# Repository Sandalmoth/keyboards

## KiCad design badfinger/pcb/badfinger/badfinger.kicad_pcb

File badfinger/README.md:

# Badfinger

__Would not recommend building__, as I made a lot of design mistakes, but it is possible. 
It's a 52 key low-profile keyboard, with slightly bigger than choc spacing, powered by regular batteries. 
Ultimately, I wanted a wireless split powered by regular 1.2V AAA batteries, and it's what I got.

The most interesting takeaway here is that the R-78S3.3-0.1 is a really handy part for making battery powered things.

## Materials
__2x PCBs__

__2x XIAO nRF52840__  

__2x Keystone 2468 Battery holder__

__2x R-78S3.3-0.1 DC-DC converter__

Finally, some m3x10, m3x6, m3 square nuts, m2x8 self tapping screws, and wires for the assembly. 
There's also a 2.2uF cap and 1uH inductor, but, I think the inductor could be replaced by a wire and the cap skipped with no real harm done, though don't quote me on that.

The DC-DC converter won't fit in it's footprint, but needs to be connected with wires and placed just below the battery holder. Looking at the case std should make it fairly clear where it goes.

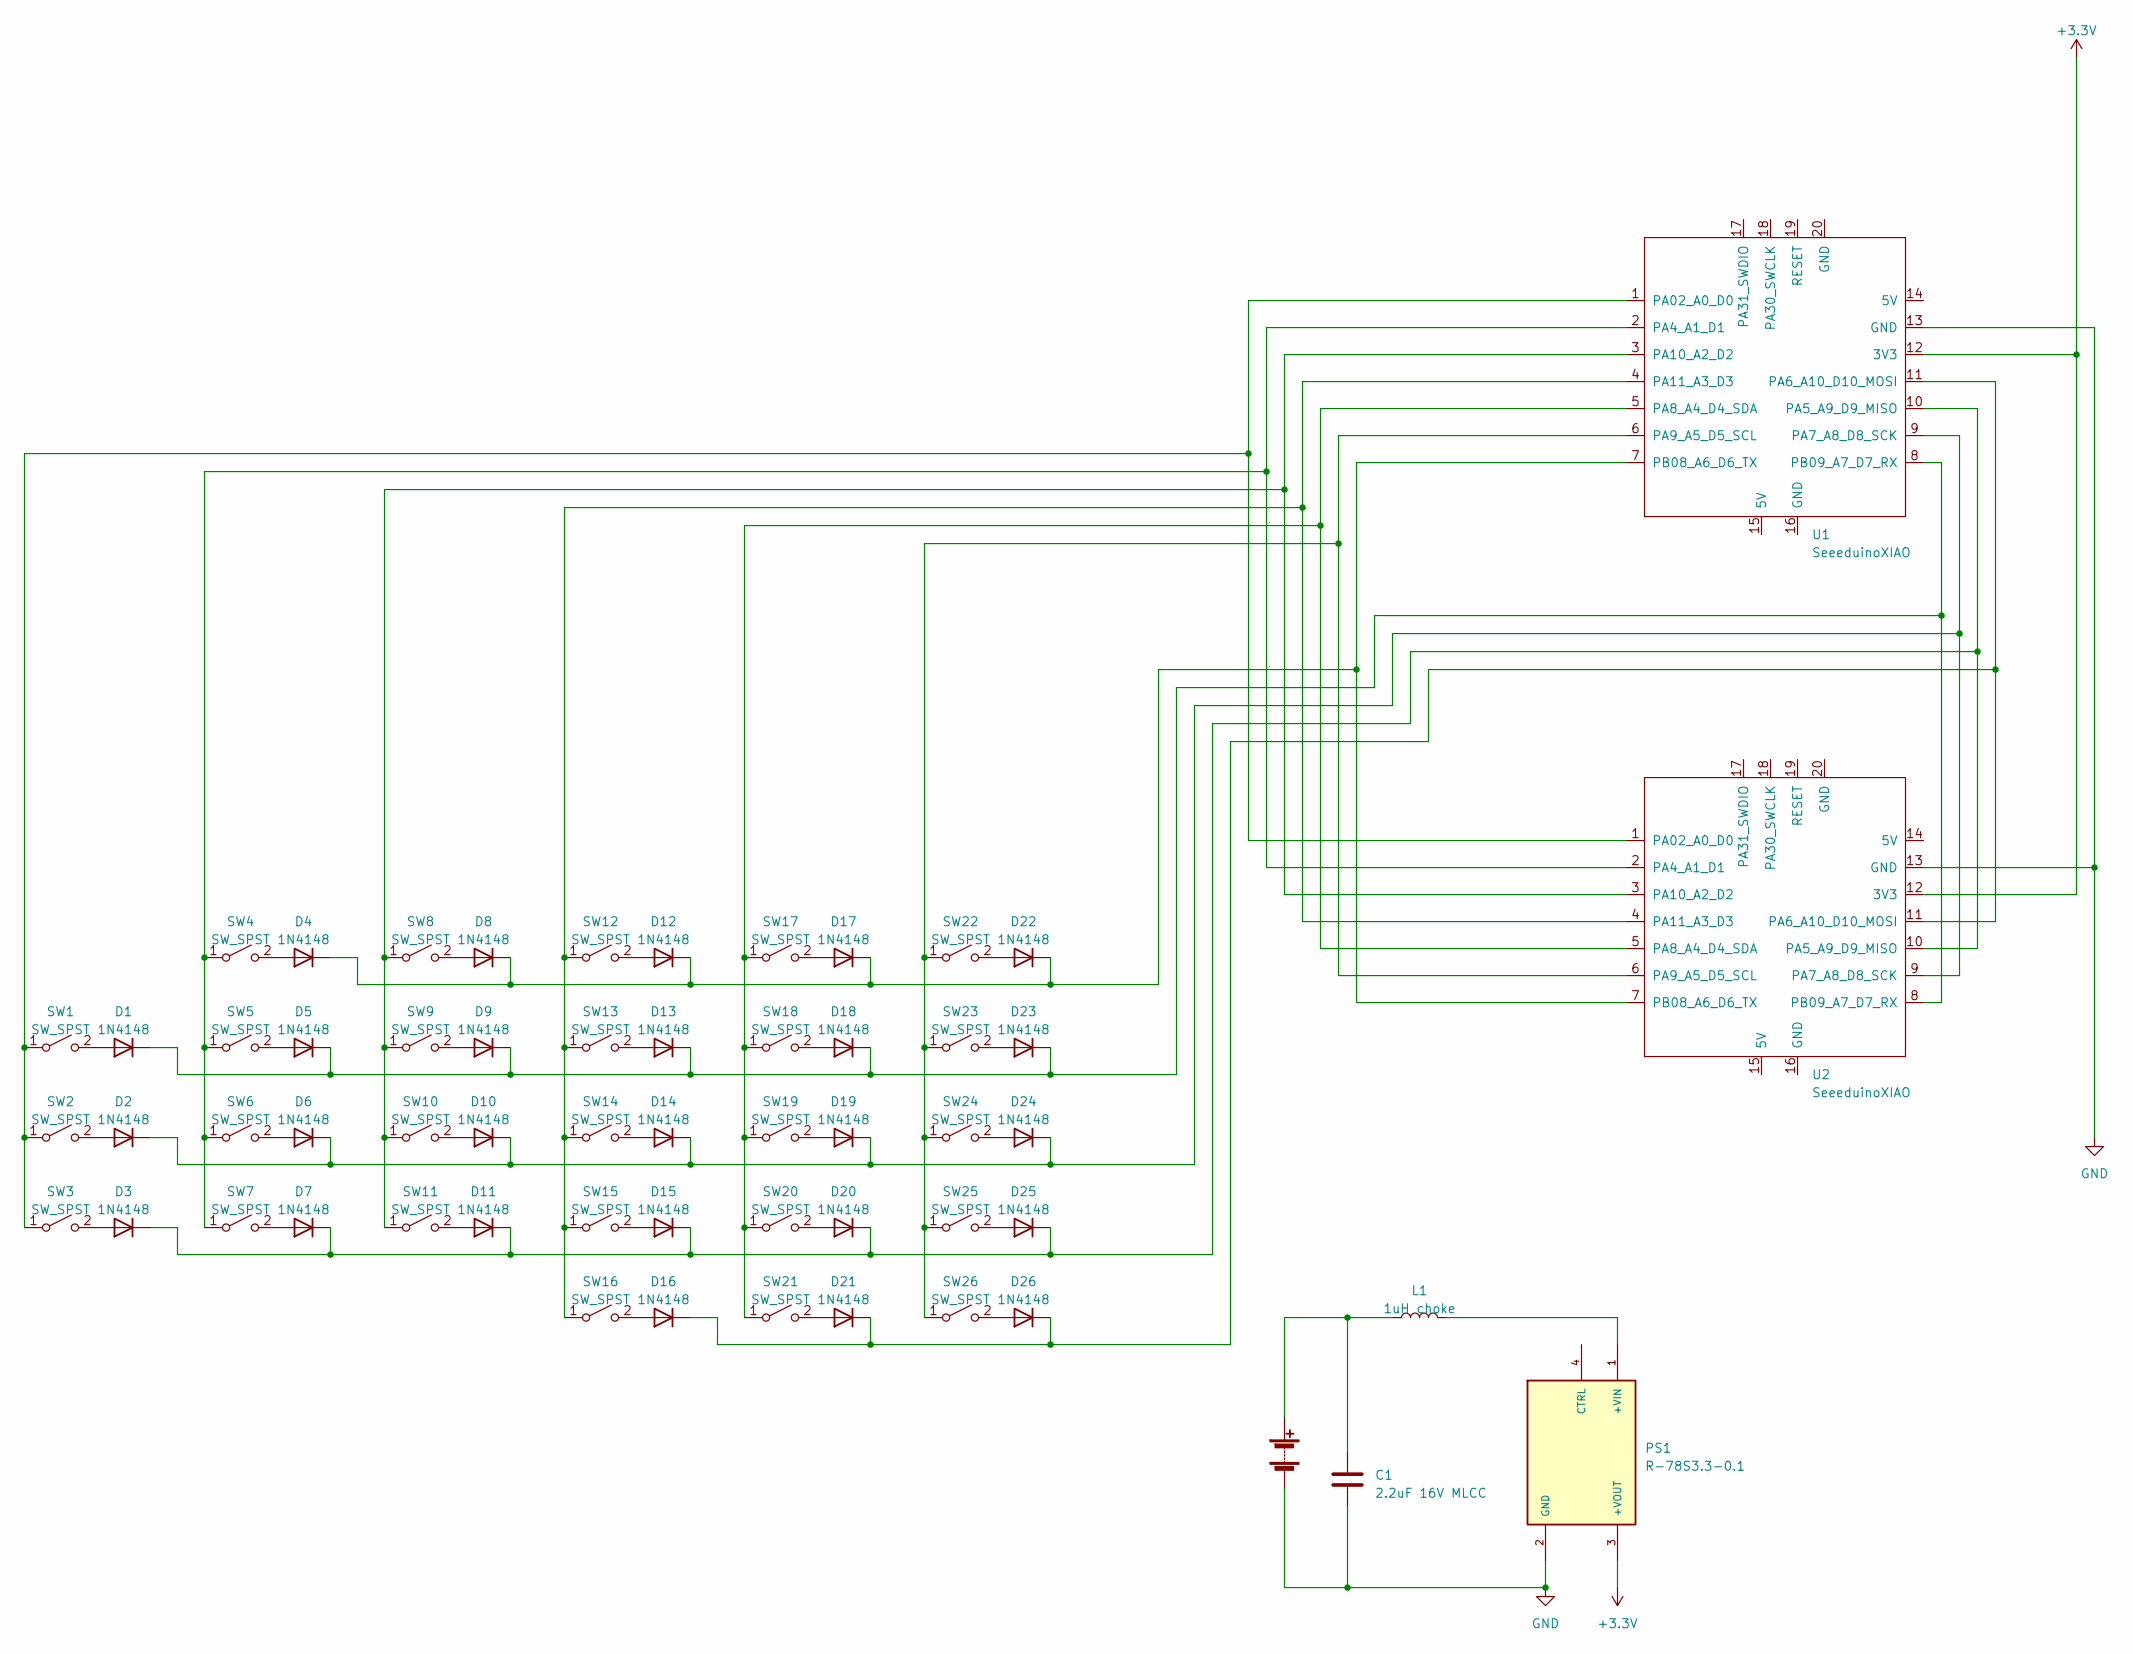
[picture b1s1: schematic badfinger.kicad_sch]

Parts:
BT1: Battery; PinHeader_1x02_P2.54mm_Vertical
C1: 2.2uF 16V MLCC; CP_Radial_D5.0mm_P2.50mm
D1, D2, D3, D4, D5, D6, D7, D8, D9, D10, D11, D12, D13, D14, D15, D16, D17, D18, D19, D20, D21, D22, D23, D24, D25, D26: 1N4148; D_DO-35_SOD27_P7.62mm_Horizontal
L1: 1uH choke; L_Axial_L9.5mm_D4.0mm_P15.24mm_Horizontal_Fastron_SMCC
PS1: R-78S3.3-0.1; CONV_R-78S3.3-0.1; PARTREV 5
SW1, SW2, SW3, SW4, SW5, SW6, SW7, SW8, SW9, SW10, SW11, SW12, SW13, SW14, SW15, SW16, SW17, SW18, SW19, SW20, SW21, SW22, SW23, SW24, SW25, SW26: SW_SPST; SW_PG1350_reversible
U1, U2: SeeeduinoXIAO; qtpy

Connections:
+3.3V: PS1.3 (+VOUT), U1.12 (3V3), U2.12 (3V3)
GND: BT1.2 (-), C1.2, PS1.2 (GND), U1.13 (GND), U2.13 (GND)
unnamed: BT1.1 (+), C1.1, L1.1
unnamed: D1.2 (A), SW1.2 (B)
unnamed: D1.1 (K), D5.1 (K), D9.1 (K), D13.1 (K), D18.1 (K), D23.1 (K), U1.8 (PB09_A7_D7_RX), U2.8 (PB09_A7_D7_RX)
unnamed: D2.2 (A), SW2.2 (B)
unnamed: D3.2 (A), SW3.2 (B)
unnamed: D4.2 (A), SW4.2 (B)
unnamed: D5.2 (A), SW5.2 (B)
unnamed: D6.2 (A), SW6.2 (B)
unnamed: D7.2 (A), SW7.2 (B)
unnamed: D8.2 (A), SW8.2 (B)
unnamed: D9.2 (A), SW9.2 (B)
unnamed: D10.2 (A), SW10.2 (B)
unnamed: D2.1 (K), D6.1 (K), D10.1 (K), D14.1 (K), D19.1 (K), D24.1 (K), U1.9 (PA7_A8_D8_SCK), U2.9 (PA7_A8_D8_SCK)
unnamed: D11.2 (A), SW11.2 (B)
unnamed: D3.1 (K), D7.1 (K), D11.1 (K), D15.1 (K), D20.1 (K), D25.1 (K), U1.10 (PA5_A9_D9_MISO), U2.10 (PA5_A9_D9_MISO)
unnamed: D12.2 (A), SW12.2 (B)
unnamed: D4.1 (K), D8.1 (K), D12.1 (K), D17.1 (K), D22.1 (K), U1.7 (PB08_A6_D6_TX), U2.7 (PB08_A6_D6_TX)
unnamed: D13.2 (A), SW13.2 (B)
unnamed: D14.2 (A), SW14.2 (B)
unnamed: D15.2 (A), SW15.2 (B)
unnamed: D16.2 (A), SW16.2 (B)
unnamed: D16.1 (K), D21.1 (K), D26.1 (K), U1.11 (PA6_A10_D10_MOSI), U2.11 (PA6_A10_D10_MOSI)
unnamed: D17.2 (A), SW17.2 (B)
unnamed: D18.2 (A), SW18.2 (B)
unnamed: D19.2 (A), SW19.2 (B)
unnamed: D20.2 (A), SW20.2 (B)
unnamed: D21.2 (A), SW21.2 (B)
unnamed: D22.2 (A), SW22.2 (B)
unnamed: D23.2 (A), SW23.2 (B)
unnamed: D24.2 (A), SW24.2 (B)
unnamed: D25.2 (A), SW25.2 (B)
unnamed: D26.2 (A), SW26.2 (B)
unnamed: L1.2, PS1.1 (+VIN)
unnamed: SW1.1 (A), SW2.1 (A), SW3.1 (A), U1.1 (PA02_A0_D0), U2.1 (PA02_A0_D0)
unnamed: SW4.1 (A), SW5.1 (A), SW6.1 (A), SW7.1 (A), U1.2 (PA4_A1_D1), U2.2 (PA4_A1_D1)
unnamed: SW8.1 (A), SW9.1 (A), SW10.1 (A), SW11.1 (A), U1.3 (PA10_A2_D2), U2.3 (PA10_A2_D2)
unnamed: SW12.1 (A), SW13.1 (A), SW14.1 (A), SW15.1 (A), SW16.1 (A), U1.4 (PA11_A3_D3), U2.4 (PA11_A3_D3)
unnamed: SW17.1 (A), SW18.1 (A), SW19.1 (A), SW20.1 (A), SW21.1 (A), U1.5 (PA8_A4_D4_SDA), U2.5 (PA8_A4_D4_SDA)
unnamed: SW22.1 (A), SW23.1 (A), SW24.1 (A), SW25.1 (A), SW26.1 (A), U1.6 (PA9_A5_D5_SCL), U2.6 (PA9_A5_D5_SCL)

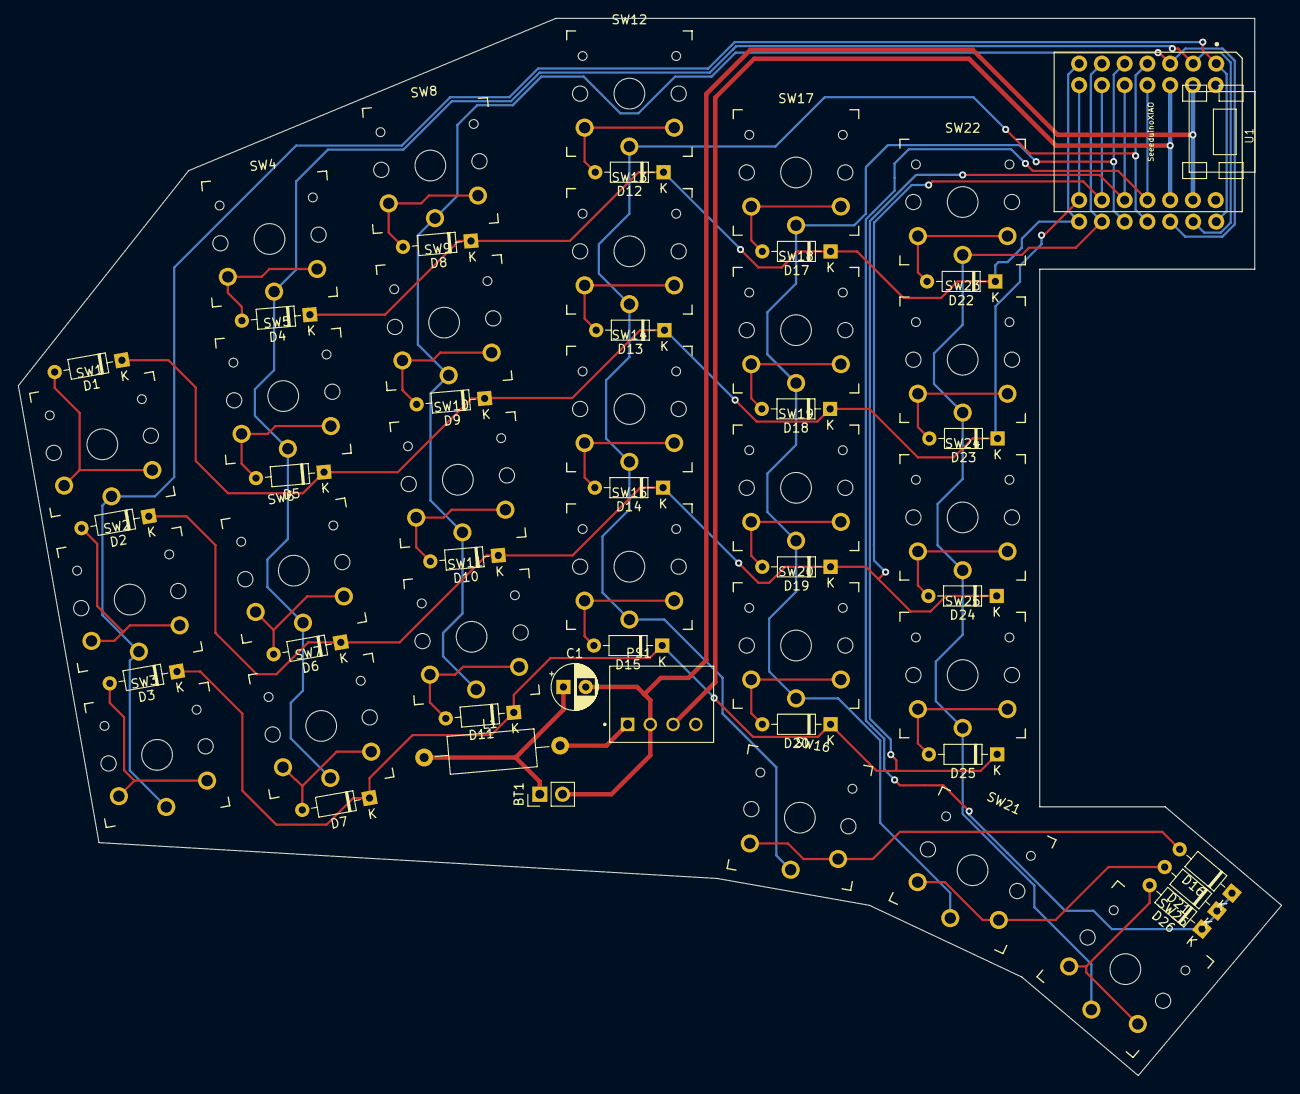
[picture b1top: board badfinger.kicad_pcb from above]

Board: 2 copper layers, 141.0 x 118.0 mm, 58 parts (1 on the bottom side), 41 nets.

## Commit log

2023-02-23 add a keyboard :)
2023-03-12 Update README.md
    Add screws for attaching bottom cover to BOM
2023-11-15 add badfinger, an aaa-powered low-profile wireless
2024-03-17 new keyboard!
2024-07-15 replace duplicate stl with the correct one
